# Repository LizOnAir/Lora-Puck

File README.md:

# Lora-Puck
A Lora module with a AHT20 sensors and LCD display to show status. I made this to discover about how to use LoRa for communication.

## Features:
- detect humidity
- detect temperature
- send data via Lora
- low power consumption
- display

## PCB

### Schematic

### Layout

Access files in [PCB folder](https://github.com/LizOnAir/Lora-Puck/tree/main/PCB).

For this design, I'm using PCBA from JLCPCB.

## CAD

Made in Fusion360.Liz
Access files in [CAD folder](https://github.com/LizOnAir/Lora-Puck/tree/main/CAD).

### Assembly
1.  Insert 4 heatset onto the 4 mounting holes in the bottom case.
2.  Insert the PCB into the bottom case.
3.  Using hot glue, stick the buttons onto the tactile switches.
4.  Align the holes of PCB onto the holes of the bottom case.
5.  Cover the top case over the bottom case.
6.  Screw them tight together.
7.  Charge the battery and hang it on somewhere to start detect temperature!!

## Firmware
I use Arduino IDE for programming.
- display
- sensors
- sending data via lora

Access files in [Firmware folder](https://github.com/LizOnAir/Lora-Puck/tree/main/Firmware).

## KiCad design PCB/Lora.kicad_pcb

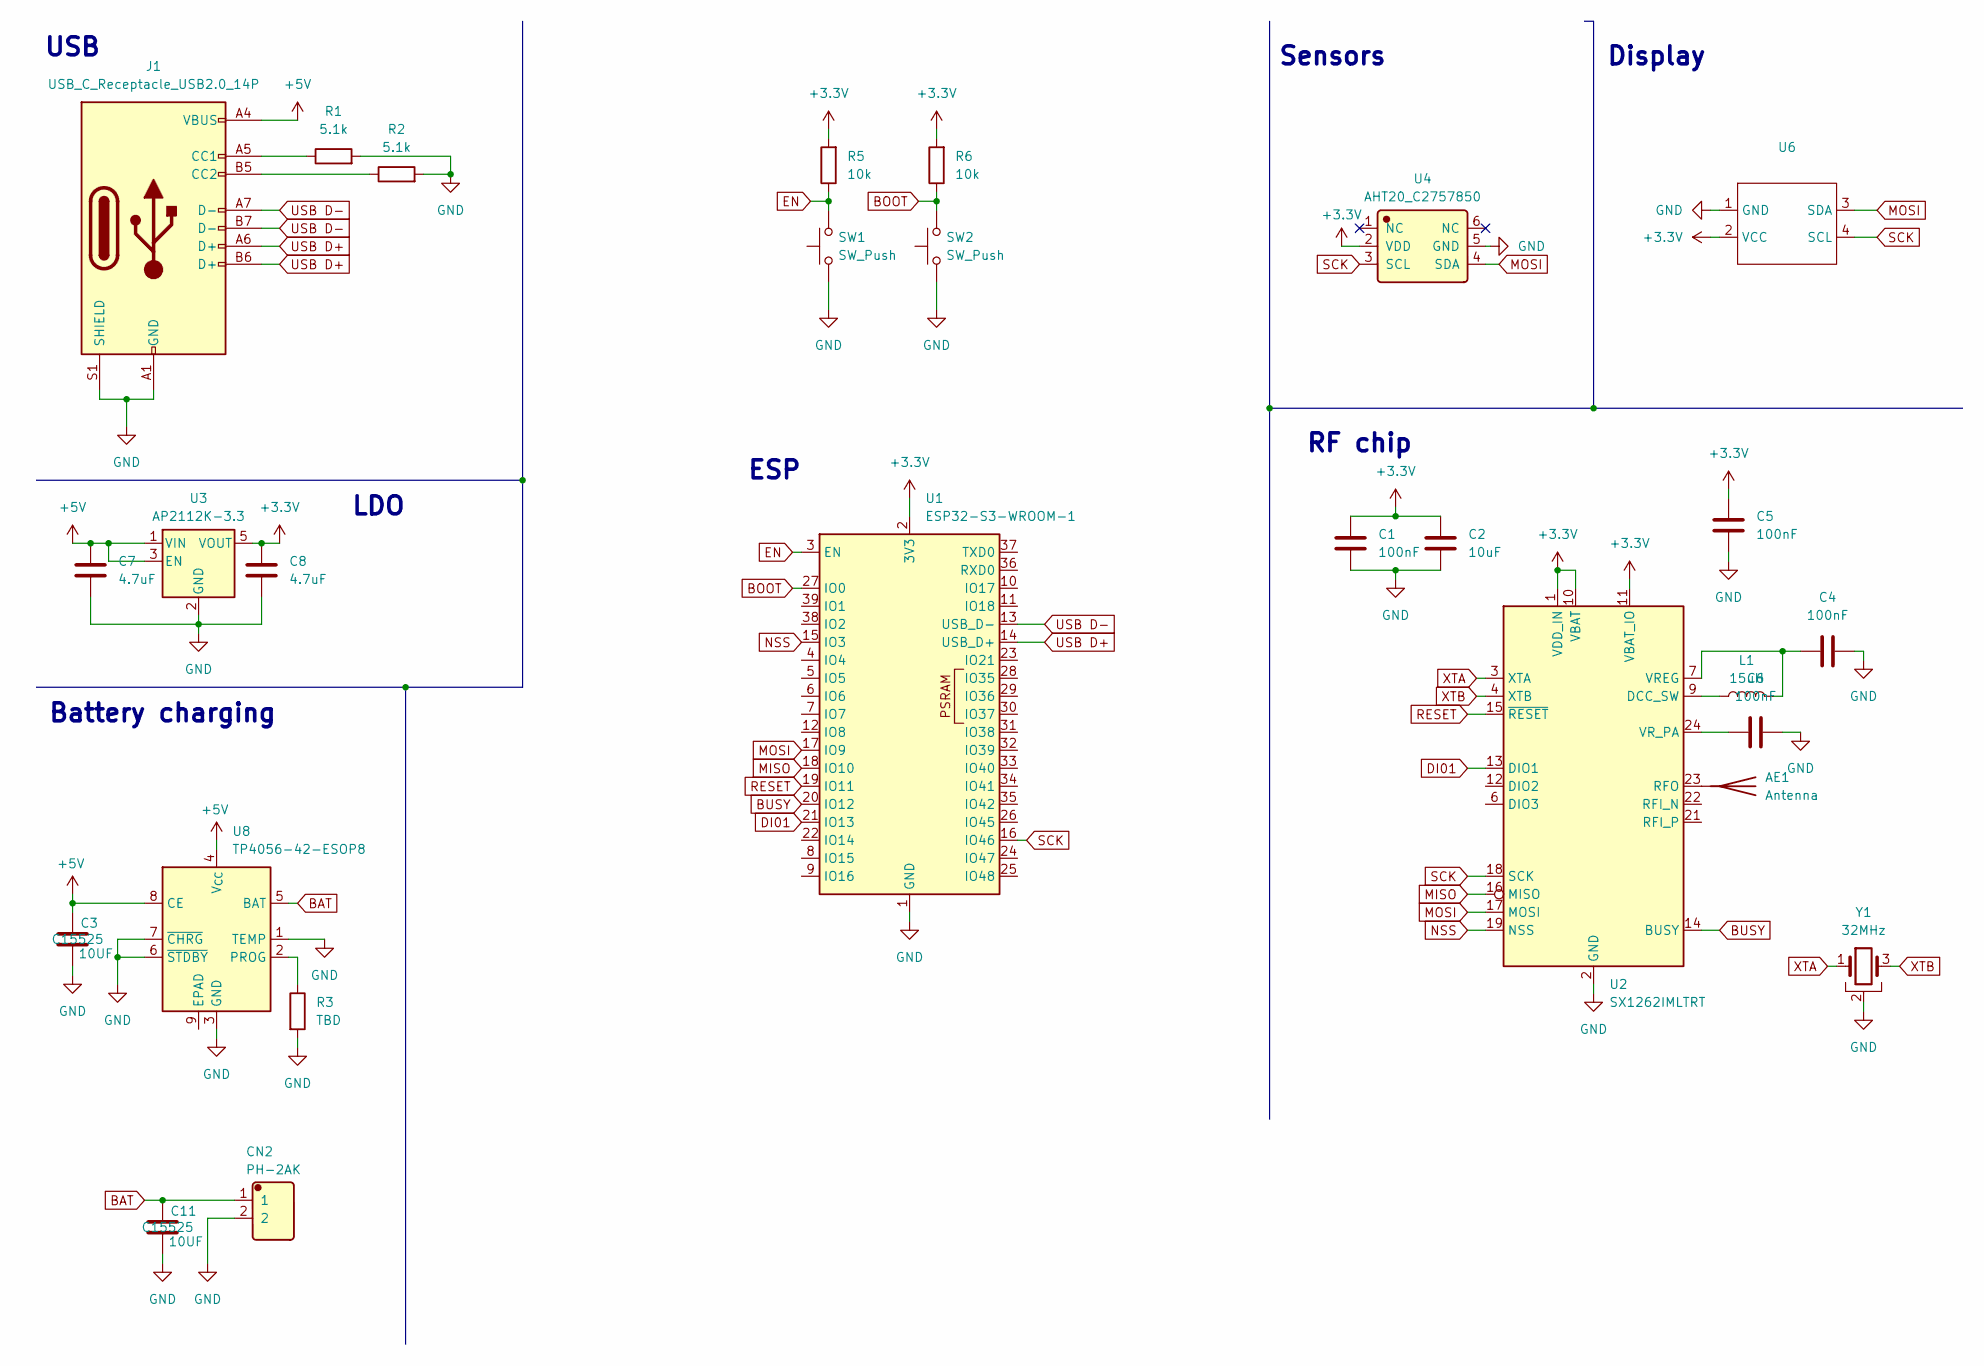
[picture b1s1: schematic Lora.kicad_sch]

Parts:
AE1: Antenna; U.FL_Hirose_U.FL-R-SMT-1_Vertical
C1, C4, C5, C6: 100nF; C_0402_1005Metric
C2: 10uF; C_0402_1005Metric
C3, C11: 10UF; C_0402_1005Metric; MNF part num C15525
C7, C8: 4.7uF; C_0402_1005Metric
CN2: PH-2AK; JST_PH_S2B-PH-K_1x02_P2.00mm_Horizontal; Manufacturer Part PH-2AK; LCSC C8886
J1: USB_C_Receptacle_USB2.0_14P; USB_C_Receptacle_G-Switch_GT-USB-7010ASV
L1: 15uH; L_0603_1608Metric
R1, R2: 5.1k; R_0402_1005Metric
R3: TBD; R_0402_1005Metric
R5, R6: 10k; R_0402_1005Metric
SW1, SW2: SW_Push; SW_SPST_TS-1088-xR020
U1: ESP32-S3-WROOM-1
U2: SX1262IMLTRT; QFN-24-1EP_4x4mm_P0.5mm_EP2.6x2.6mm
U3: AP2112K-3.3; SOT-23-5
U4: AHT20_C2757850; Manufacturer Part AHT20; LCSC C2757850
U6: PinHeader_1x04_P2.54mm_Vertical
U8: TP4056-42-ESOP8; SOIC-8-1EP_3.9x4.9mm_P1.27mm_EP2.41x3.3mm_ThermalVias
Y1: 32MHz; Crystal_SMD_Abracon_ABM10-4Pin_2.5x2.0mm

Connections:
+3.3V: C1.1, C2.1, C5.2, C8.2, R5.2, R6.2, U1.2 (3V3), U2.1 (VDD_IN), U2.10 (VBAT), U2.11 (VBAT_IO), U3.5 (VOUT), U4.2 (VDD), U6.2 (VCC)
+5V: C3.1, C7.2, J1.A4 (VBUS), J1.A9 (VBUS), J1.B4 (VBUS), J1.B9 (VBUS), U3.1 (VIN), U3.3 (EN), U8.4 (V_{CC}), U8.8 (CE)
BAT: C11.1, CN2.1, U8.5 (BAT)
BOOT: R6.1, SW2.2, U1.27 (IO0)
BUSY: U1.20 (IO12), U2.14 (BUSY)
DI01: U1.21 (IO13), U2.13 (DIO1)
EN: R5.1, SW1.2, U1.3 (EN)
GND: C1.2, C2.2, C3.2, C4.1, C5.1, C6.1, C7.1, C8.1, C11.2, CN2.2, J1.A1 (GND), J1.A12 (GND), J1.B1 (GND), J1.B12 (GND), J1.S1 (SHIELD), R1.2, R2.2, R3.2, SW1.1, SW2.1, U1.1 (GND), U1.40 (GND), U1.41 (GND), U2.2 (GND), U2.5 (GND), U2.8 (GND), U2.20 (GND), U2.25 (GND), U3.2 (GND), U4.5 (GND), U6.1 (GND), U8.1 (TEMP), U8.3 (GND), U8.6 (~STDBY), U8.7 (~CHRG), Y1.2
MISO: U1.18 (IO10), U2.16 (MISO)
MOSI: U1.17 (IO9), U2.17 (MOSI), U4.4 (SDA), U6.3 (SDA)
NSS: U1.15 (IO3), U2.19 (NSS)
unnamed: AE1.1 (A), U2.23 (RFO)
unnamed: J1.A5 (CC1), R1.1
unnamed: J1.B5 (CC2), R2.1
unnamed: L1.1, U2.9 (DCC_SW)
unnamed: C4.2, L1.2, U2.7 (VREG)
unnamed: C6.2, U2.24 (VR_PA)
unnamed: R3.1, U8.2 (PROG)
RESET: U1.19 (IO11), U2.15 (~RESET)
SCK: U1.16 (IO46), U2.18 (SCK), U4.3 (SCL), U6.4 (SCL)
USB D+: J1.A6 (D+), J1.B6 (D+), U1.14 (USB_D+)
USB D-: J1.A7 (D-), J1.B7 (D-), U1.13 (USB_D-)
XTA: U2.3 (XTA), Y1.1
XTB: U2.4 (XTB), Y1.3

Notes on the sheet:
USB
ESP
Display
LDO
Sensors
RF chip
Battery charging

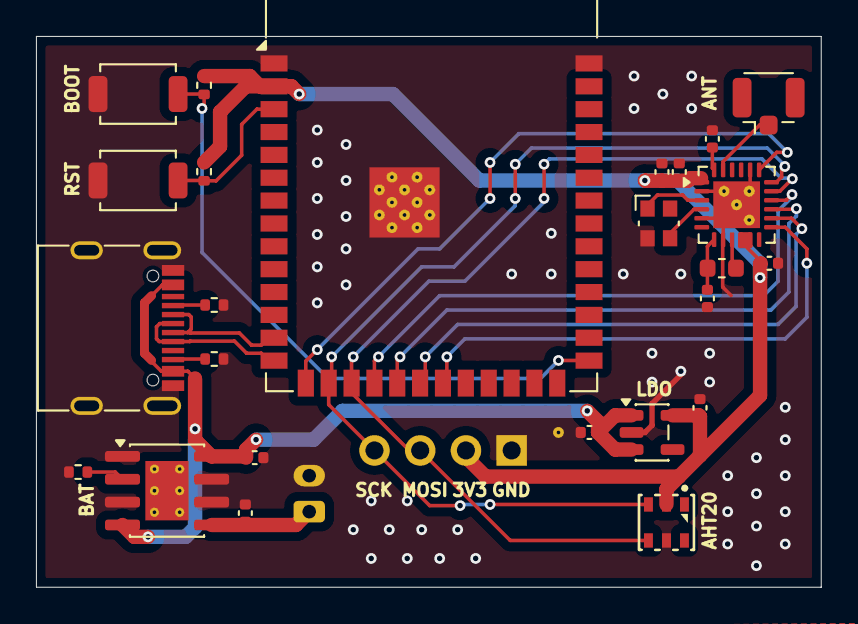
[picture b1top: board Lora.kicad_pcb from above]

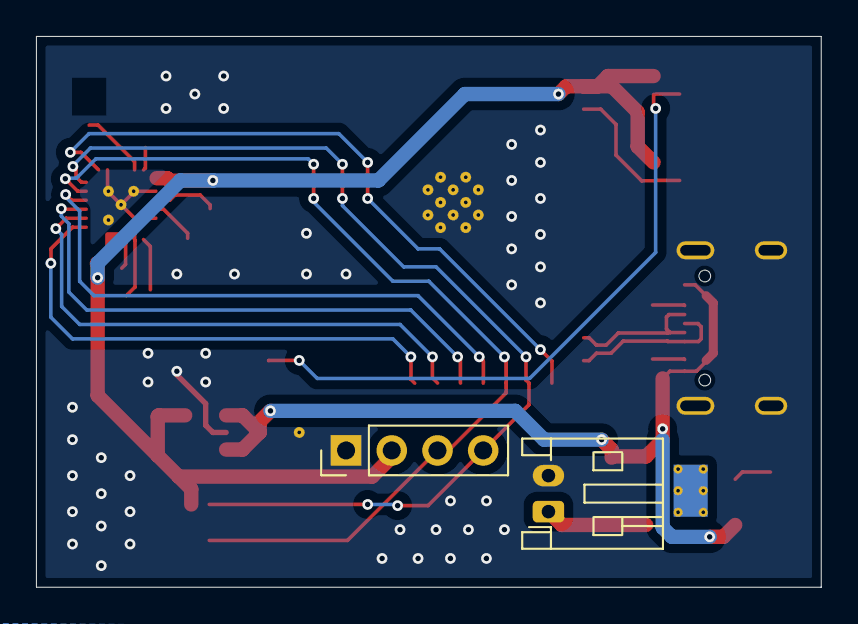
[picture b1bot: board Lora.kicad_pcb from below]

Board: 2 copper layers, 43.6 x 30.6 mm, 27 parts (2 on the bottom side), 24 nets.

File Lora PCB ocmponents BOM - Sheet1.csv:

Designator,Comment,Footprint,Manufacturer,Footprint,JLCPCB Part #,Product link,Lib Type,Rec. Order Qty,Unit Price ($),Total Price ($)
"C11,C2,C3",10UF,402,Samsung Electro-Mechanics,402,C15525,https://jlcpcb.com/partdetail/16204-CL05A106MQ5NUNC/C15525,Basic,20,0.0256,0.512
J1,USB_C_Receptacle_USB2.0_14P,USB_C_Receptacle_G-Switch_GT-USB-7010ASV,SHOU HAN,USB_C_Receptacle_G-Switch_GT-USB-7010ASV,C2765186,https://jlcpcb.com/partdetail/SHOUHAN-TYPE_C_16PIN_2MD_073/C2765186,Extended,3,0.0743,0.2229
"SW1,SW2",SW_Push,SW_SPST_TS-1088-xR020,XUNPU,SW_SPST_TS-1088-xR020,C720477,https://jlcpcb.com/partdetail/XUNPU-TS_1088AR02016/C720477,Basic,8,0.0556,0.4448
L1,15uH,603,microgate,603,C486329,https://jlcpcb.com/partdetail/microgate-MGFL1608F150MTLF/C486329,Extended,6,0.0384,0.2304
"R1,R2",5.1k,402,UNI-ROYAL(Uniroyal Elec),402,C25905,https://jlcpcb.com/partdetail/26648-0402WGF5101TCE/C25905,Basic,20,0.0026,0.052
Y1,32MHz,Crystal_SMD_Abracon_ABM10-4Pin_2.5x2.0mm,NDK,Crystal_SMD_Abracon_ABM10-4Pin_2.5x2.0mm,C843260,https://jlcpcb.com/partdetail/NDK-NX2016SA_32MHZ_STD_CZS5/C843260,Extended,5,0.3518,1.759
"R5,R6",10k,402,UNI-ROYAL(Uniroyal Elec),402,C25744,https://jlcpcb.com/partdetail/26487-0402WGF1002TCE/C25744,Basic,20,0.0031,0.062
U2,SX1262IMLTRT,QFN-24-1EP_4x4mm_P0.5mm_EP2.6x2.6mm,SEMTECH,QFN-24-1EP_4x4mm_P0.5mm_EP2.6x2.6mm,C191341,https://jlcpcb.com/partdetail/SEMTECH-SX1262IMLTRT/C191341,Extended,2,3.1938,6.3876
"C7,C8",4.7uF,402,Samsung Electro-Mechanics,402,C23733,https://jlcpcb.com/partdetail/24469-CL05A475MP5NRNC/C23733,Basic,20,0.0233,0.466
U8,TP4056-42-ESOP8,SOIC-8-1EP_3.9x4.9mm_P1.27mm_EP2.41x3.3mm_ThermalVias,TOPPOWER(Nanjing Extension Microelectronics),SOIC-8-1EP_3.9x4.9mm_P1.27mm_EP2.41x3.3mm_ThermalVias,C16581,https://jlcpcb.com/partdetail/17264-TP4056_42ESOP8/C16581,Extended,2,0.1843,0.3686
"C1,C4,C5,C6",100nF,402,Samsung Electro-Mechanics,402,C1525,https://jlcpcb.com/partdetail/1877-CL05B104KO5NNNC/C1525,Basic,20,0.0051,0.102
U3,AP2112K-3.3,SOT-23-5,TECH PUBLIC,SOT-23-5,C23380830,https://jlcpcb.com/partdetail/TECHPUBLIC-AP2112K_33TRG1/C23380830,Extended,5,0.1104,0.552
U4,AHT20_C2757850,AHT20_C2757850,Aosong (Guangzhou) Elec,AHT20_C2757850,C2757850,https://jlcpcb.com/partdetail/Aosong_Guangzhou_Elec-AHT20/C2757850,Extended,2,0.7944,1.5888
U1,ESP32-S3-WROOM-1,ESP32-S3-WROOM-1,Espressif Systems,ESP32-S3-WROOM-1,C2913202,https://jlcpcb.com/partdetail/3198300-ESP32_S3_WROOM_1N16R8/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,Extended,2,5.1335,10.267
AE1,Antenna,U.FL_Hirose_U.FL-R-SMT-1_Vertical,HJ Tech,U.FL_Hirose_U.FL-R-SMT-1_Vertical,C2831497,https://jlcpcb.com/partdetail/HJTech-434MHz_SMA_Flexibleante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,Extended,2,1.8699,3.7398
PCB Assembled Qty：2,,,,,,,,,,"Est. Total Price：26.7920
 (Pre-order parts require a quotation for final pricing.)"
